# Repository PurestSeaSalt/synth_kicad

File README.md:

# synth_kicad
## GitHub Action to compile KiCad files

This repo contains an example custom PCB designed in KiCAD 5 with settings appropriate for PCB manufacture and assembly by JLCPCB. It also contains a GitHub workflow that generates the files needed by JLCPCB: gerbers, BOM, & position file. The workflow additionally generates a manual order BOM,  interactive BOM, and PDF export of the schematic. The manual order BOM includes components in the schematic not assembled by JLCPCB, such as board components not available through JLCPCB, enclosure, hardware, etc. The interactive BOM is an html document that assists in identifying component locations on the PCB for manual assembly.

## Setup Repository GitHub Actions Permissions

The workflow requires read/write access to the new repository to execute successfully.

In the new repository navigate to ```Settings```, and open the ```Actions``` > ```General``` page.

In the ```Workflow permissions``` section select ```Read and write permissions```

## New Repository Cleanup

The newly created repository will include the ```Example_Design``` example PCB design from the template repo. Files for this need to be removed and files for the new design need created. This is best done in a local clone of the new repository on your PC.

Using your Git client (Fork, GitHub Desktop, etc.) clone your new repository to a local folder on your PC.

Eventually this file, ```README.md```, should be replaced/updated with details for the new project. Consider keeping the ```Placing Orders``` and ```Failed Workflow Troubleshooting``` sections so instructions for ordering the design and troubleshooting workflow issues are readily available.

Update ```description``` and ```ownership``` entries in ```APM.yml```.

## New KiCAD Project Creation

Open the KiCAD 8 application.

In the KiCAD Project Manager select ```File``` > ```New``` > ```Project```.

In the ```Create New Project``` dialog check the box for ```Create a new directory for the project```. (Missing this step will break the GitHub workflow functionality.)

Navigate to the ```KiCadProjects``` folder under your cloned repository directory, Enter a name for your KiCAD project, and select ```Save```.

## KiCAD Schematic Setup

The GitHub workflow requires additional schematic symbol fields beyond the KiCAD defaults.

In the KiCAD schematic editor (Eeschema) select ```Preferences``` > ```Preferences...```

In the ```Eeschema``` > ```Field Name Templates``` section add the following entries:

- Part No
- Link
- LCSC
- Note

Check the ```URL``` box for the Link field.

This will add the above fields to every new symbol added to the schematic.

Note: These are KiCAD application settings and apply across all projects. If multiple users are contributing to the design, they will each need to apply these settings.

These fields can also be added to all current components in the KiCAD schematic editor under ```Tools``` > ```Edit Symbol Fields...```

For each component in the schematic either LCSC, for parts to be assembled by JLCPCB, or Part No, for parts to not be assembled by JLCPCB, must be filled out. Additionally the fields Link & Note can be filled out to provide additional information in the manually ordered parts BOM for parts to not be assembled by JLCPCB.

## KiCAD PCB Setup

The PCB design needs to be setup to match the capabilities of JLCPCB. These settings can be copied from the ```Example_Design``` in the template repo.

In the KiCAD PCB editor (PCBNew) select ```File``` > ```Board Setup...```

In the bottom left of the ```Board Setup dialog```, select ```Import Settings...```

In the bottom left of the ```Import Settings``` dialog click ```Select All```.

In the ```Import from``` field navigate to the folder ```KiCadProjects\Example_Design``` under your cloned repository directory and select ```Example_Design.pro```.

Select ```Import Settings```.

## Setup For Multiple Boards

Projects with more than one PCB, for example a motherboard and one or more daughter boards are supported. Follow the steps under ```New KiCAD Project Creation```, ```KiCAD Schematic Setup```, & ```KiCAD PCB Setup``` to create and setup a separate KiCad project for each board.

## Remove Example Design KiCad Project

After setting up the new KiCad project(s), the Example_Design files are no longer needed and the ```KiCadProjects\Example_Design``` folder can be deleted.

## Selecting Parts For JLCPCB Assembly

JLCPCB's parts catalog can be accessed at [jlcpcb.com/parts](https://jlcpcb.com/parts).

Prior to selecting parts for JLCPCB assembly it is recommended to review JLCPCB's PCB Assembly FAQs [Part 1](https://jlcpcb.com/help/article/98-pcb-assembly-faqs) & [Part 2](https://jlcpcb.com/help/article/39-pcb-assembly-faqs-part-2). Pay specific attention to the section related to Basic vs. Extended parts and the section related to polarity of components.

Recommended part selection priorities should be:

- Only SMD parts if possible (Avoid hand assembly & hand soldering fees)
- Prefer Basic parts vs. Extended parts (Avoid additional setup fees)
- Prefer parts with large inventories ( Avoid pre-order process. See ```NOTE``` under ```Placing Orders``` )

Once a part is selected enter the JLCPCB Part # in the LCSC field of the component in the KiCAD schematic.

## Notes on Footprint Rotation

JLCPCB uses the orientation of the component in the tape & reel when the feed direction is up as the zero degree reference. ( See JLCPCB's PCB Assembly FAQ [Part 2](https://jlcpcb.com/help/article/39-pcb-assembly-faqs-part-2). ) KiCAD uses the footprint orientation as the zero degree reference. For many standard component packages, common tape & reel orientations do not match the standard KiCAD footprint orientations. However, the position file generation tool of the GitHub workflow applies corrections for several standard packages to address this. ( See the internal list of rotations at the end of the [Notes about the position file](https://github.com/INTI-CMNB/KiBot#notes-about-the-position-file) section in the KiBot documentation. )

Consider an example design using an SOIC-8 component oriented with pin 1 at the top right. JLCPCB's PCB Assembly FAQ [Part 2](https://jlcpcb.com/help/article/39-pcb-assembly-faqs-part-2) indicates that for On Semiconductors SOIC-8 packages JLCPCB's zero orientation has pin 1 at the bottom-left, which would require a rotation of 180° to put pin 1 at the top-right.

KiCAD's default SOIC-8 footprint, ```SOIC-8_3.9x4.9mm_P1.27mm```, has pin 1 at the top-left. The footprint would be rotated 270° to put pin 1 at the top-right.

The footprint name, ```SOIC-8_3.9x4.9mm_P1.27mm```, matches the ```^SOIC-``` line in the internal list of rotations which adds 270° to the KiCAD rotation. This results in a total rotation of 180° in the position file, which matches the rotation expected by JLCPCB.

## Placing Orders

Prior to preparing to place orders, be sure all design changes are committed and pushed to the GitHub repository.

To generate files required for ordering parts navigate to the ```Issues``` page of the Github repository, and select ```New issue```.

To the right of ```Order and Assembly Files Request``` select ```Get started```.

Replace the ```[Your descriptor here]``` text in the title with a descriptor for your order. The beginning of the title must remain as ```Order and Assembly Files Request:``` in order to be processed.

Enter the quantity of boards you plan to order.

If applicable, select a board variant.

Select ```Submit new issue```.

A new run of the ```Process Order and Assembly Files Request``` workflow will be initiated. After a few minutes the run should complete. If successful the workflow run will add a comment with a link to the workflow run and close the issue. Open the workflow run to access the generated files. The workflow run can also be found under the repository's ```Actions``` page. The workflow run will have the same title as the requesting issue.

At the bottom of the workflow run page is a list of links to the generated files. Selecting ```Manual_Order_and_Assembly_Files``` will download a zip of the manual order BOM, interactive BOM, and schematic. Selecting ```JLCPCB_Files``` will download a zip file of the files needed for the JLCPCB order. These zip files will contain a subfolder for each KiCad project under ```KiCadProjects```.

```NOTE:``` If required parts are not in stock at JLCPCB you will need to use their pre-order process. Before ordering the PCB, parts not in JLCPCB's inventory must be ordered to your personal JLCPB parts library. When ordering these parts the initial price paid is an estimate. The parts will then be quoted. If the quote is less than the estimate the difference will be refunded. If the quote is greater than the estimate a supplemental payment must be made for the difference. The parts will then be purchased and delivered to your parts library at JLCPCB. Once all  parts are in JLCPCB's inventory or your parts library the PCB can be ordered. See [this](https://jlcpcb.com/help/article/49-how-to-build-your-own-parts-library-in-jlcpcb) JLCPCB help article for further details.

## Failed Workflow Troubleshooting

If the workflow run fails, showing a red X icon instead of a green check icon, first verify the request was filled out properly. Second look if the electrical rules check (ERC) and/or design rules check (DRC) failed. These workflow steps perform the same checks as the KiCAD schematic editor (Eescheema) for ERC and PCB editor (PCBNew) for DRC. Run these in the applications and clear all errors before proceeding.

The most common ERC error is a not driven pin error. Pins that have their ```Electrical type``` set as ```Power input``` such as power and ground pins, including the ```GND``` symbol must be connected to a pin with an ```Electrical type``` of ```Power output```. Often the symbol/pin where power & ground are supplied is a generic connector without a ```Power output``` pin. The ```PWR_FLAG``` symbol can be added to the schematic in these locations to clear this error.

## Board Variants

In certain cases it is desirable to have variability within a PCB design. Components may be added, excluded, or substituted as needed to meet various design needs. Variants can be supported through additional fields in the KiCAD schematic and minor modification of the GitHub workflow files.

NOTE: If variants are used by more than one KiCad project in the repo they must be common. When generating order files only one variant can be selected. Any project that does not have the selected variant defined will use the default variant.

### Defining Board Variants

Each board variant is identified by two unique names. One is the name used within KiCAD documents. The other is the name used by the GitHub workflow. These can (but, don't need to) be the same name. Two .yaml files in the repository need modification to define a new variant: ```Config.kibot.yaml``` and ```.github/ISSUE_TEMPLATE/Order_and_Assembly_Files_Request.yaml```.

In ```Config.kibot.yaml``` find the section below

```yaml
variants:
  - name: 'Default'
    comment: 'No variant applied'
    type: kibom
    pre_transform: '_rot_footprint'
```

The ```'Default'``` variant is already defined. This variant does not have any components added, excluded, or substituted. For each new variant add lines similar to below after the ```'Default'``` variant.

```yaml
  - name: 'Low_Spec_Variant'    # Workflow name of variant.
    comment: 'Feature reduced version of design'    # Short description of variant.
    type: kibom    # Do not change this.
    file_id: _Low_Spec    #Suffix included in filename for files generated with this variant.
    variant: Low_Spec    #KiCAD name of variant.
    pre_transform:    # Do not change these.
      - '_var_rename'
      - '_rot_footprint'
```

Insure ```- name``` of the new variant is indented the same as ```- name``` of the default variant and all indentation relative to ```- name``` is maintained as shown here.

Set ```name```, ```comment```, ```file_id```, and ```variant``` to appropriate values. Only ```comment``` may include spaces.

In ```.github/ISSUE_TEMPLATE/Order_and_Assembly_Files_Request.yaml``` find the section below

```yaml
  - type: dropdown
    id: Board_Variant
    attributes:
      label: 'Board_Variant'
      multiple: false
      options:
        - 'Default'
```

For each new variant add a line consisting of '```- [Workflow Name of Variant]```' below and at the same indentation lavel as ```-'Default'``` where ```[Workflow Name of Variant]``` matches the value of ```name``` that was entered in ```Config.kibot.yaml```.

For example, ```- 'Low_Spec_Variant'```

### Adding / Excluding Components In Variants

For any component that is added or excluded from any specific variants, add a field named Config to the symbol in the KiCAD schematic. To add a component to a specific variant enter ```+[KiCAD Name of Variant]``` in the Config field. To remove a component from a specific variant enter ```-[KiCAD Name of Variant]``` in the Config field. If a component is added or removed from multiple variants they can each be added separated by a comma.

For example if R1 should be present in the ```Default``` variant, but not in ```VariantOne``` or ```VariantTwo``` and R2 should be present only in ```VariantTwo``` then the Config field for the two components should be:

|Reference|Config|
|---|---|
|R1|-VariantOne, -VariantTwo|
|R2|+VariantTwo|

### Replacing Components In Variants

To replace a component the default and substituted part(s) must share a common schematic symbol and footprint. The substituted part will have different values for fields like: Value, Part No, LCSC and possibly others. This is accomplished by adding a new field which is named as ```[KiCAD Name of Variant]```:```[Name of Field To Replace]```. A component may have the same or different substituted parts for each variant.

For example if D1 is a green LED with a JLCPCB part # of C2297 and is to be replaced with a red LED with a JLCPCB Part # of C84256 in variant Red_LED, or a yellow LED with a JLCPCB Part # of C2296 in variant Yellow_LED, then the LCSC field would have a value of C2297. Additional fields RED_LED:LCSC with a value of C84256 and Yellow_LED:LCSC with a value of C2296 would be added.

|Reference|LCSC|Red_LED:LCSC|Yellow_LED:LCSC|
|---|---|---|---|
|D1|C2297|C84256|C2296|

## Credits

The GitHub workflow in this repository relies on the KiBot project. [INTI-CMNB/KiBot](https://github.com/INTI-CMNB/KiBot)

## Useful References

KiCAD Tutorial: [Intro to KiCAD - YouTube](https://www.youtube.com/playlist?list=PLEBQazB0HUyR24ckSZ5u05TZHV9khgA1O)

JLCPCB Parts Catalog: [jlcpcb.com/parts](https://jlcpcb.com/parts)

JLCPCB Help Articles: [jlcpcb.com/help/catalog](https://jlcpcb.com/help/catalog)

KiBot GitHub Page [INTI-CMNB/KiBot](https://github.com/INTI-CMNB/KiBot)

easyeda2kicad GitHub Page [easyeda2kicad.py](https://github.com/uPesy/easyeda2kicad.py)

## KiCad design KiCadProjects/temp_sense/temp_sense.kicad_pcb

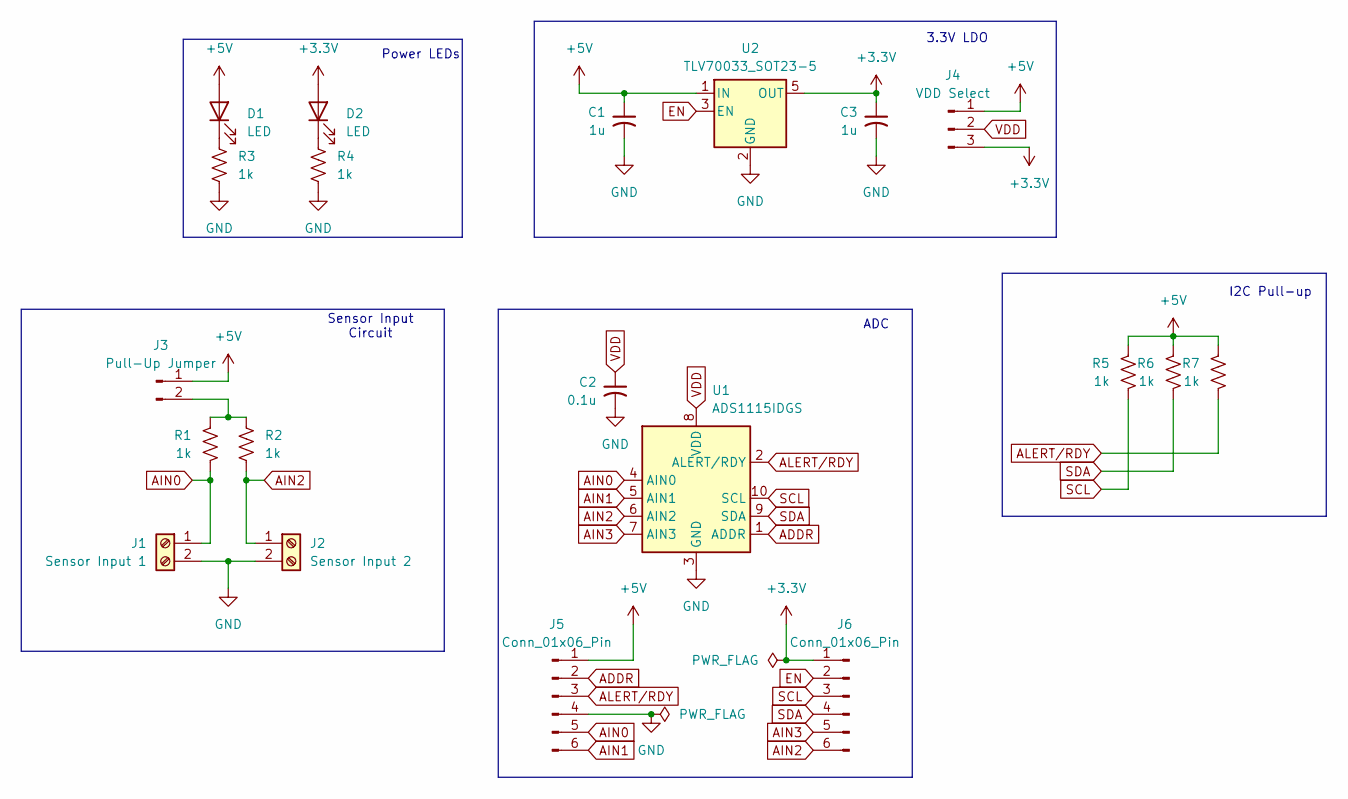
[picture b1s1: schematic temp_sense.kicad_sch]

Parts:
C1, C3: 1u; C_0603_1608Metric_Pad1.08x0.95mm_HandSolder; LCSC C15849
C2: 0.1u; C_0603_1608Metric_Pad1.08x0.95mm_HandSolder; LCSC C14663
D1, D2: LED; LED_0603_1608Metric; LCSC C19171390
J1: Sensor Input 1; TerminalBlock_TE_282834-2_1x02_P2.54mm_Horizontal
J2: Sensor Input 2; TerminalBlock_TE_282834-2_1x02_P2.54mm_Horizontal
J3: Pull-Up Jumper; PinHeader_1x02_P2.54mm_Vertical
J4: VDD Select; PinHeader_1x03_P2.54mm_Vertical
J5, J6: Conn_01x06_Pin; PinHeader_1x06_P2.54mm_Vertical
R1, R2, R3, R4, R5, R6, R7: 1k; R_0603_1608Metric_Pad0.98x0.95mm_HandSolder; LCSC C22548
U1: ADS1115IDGS; TSSOP-10_3x3mm_P0.5mm; LCSC C37593
U2: TLV70033_SOT23-5; SOT-23-5; LCSC C11337

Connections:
+3.3V: C3.1, D2.2 (A), J4.3, J6.1, U2.5 (OUT)
+5V: C1.1, D1.2 (A), J3.1, J4.1, J5.1, R5.1, R6.1, R7.1, U2.1 (IN)
ADDR: J5.2, U1.1 (ADDR)
AIN0: J1.1, J5.5, R1.2, U1.4 (AIN0)
AIN1: J5.6, U1.5 (AIN1)
AIN2: J2.1, J6.6, R2.2, U1.6 (AIN2)
AIN3: J6.5, U1.7 (AIN3)
ALERT/RDY: J5.3, R7.2, U1.2 (ALERT/RDY)
EN: J6.2, U2.3 (EN)
GND: C1.2, C2.2, C3.2, J1.2, J2.2, J5.4, R3.2, R4.2, U1.3 (GND), U2.2 (GND)
unnamed: D1.1 (K), R3.1
unnamed: D2.1 (K), R4.1
unnamed: J3.2, R1.1, R2.1
SCL: J6.3, R5.2, U1.10 (SCL)
SDA: J6.4, R6.2, U1.9 (SDA)
VDD: C2.1, J4.2, U1.8 (VDD)

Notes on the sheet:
I2C Pull-up
Sensor Input Circuit
Power LEDs
3.3V LDO
ADC

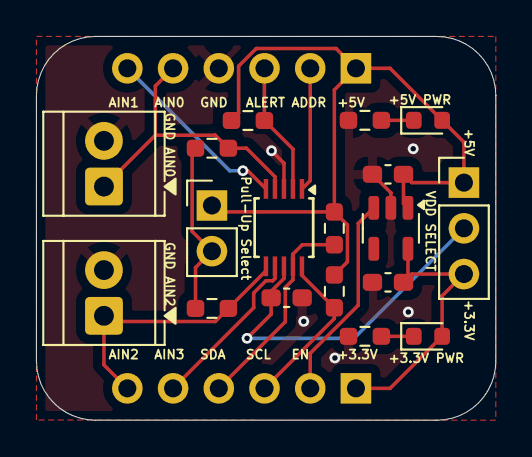
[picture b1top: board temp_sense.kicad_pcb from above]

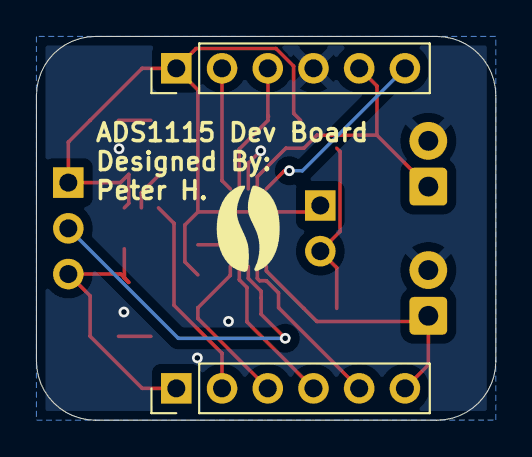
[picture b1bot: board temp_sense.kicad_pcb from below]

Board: 2 copper layers, 25.5 x 21.3 mm, 20 parts (2 on the bottom side), 16 nets.

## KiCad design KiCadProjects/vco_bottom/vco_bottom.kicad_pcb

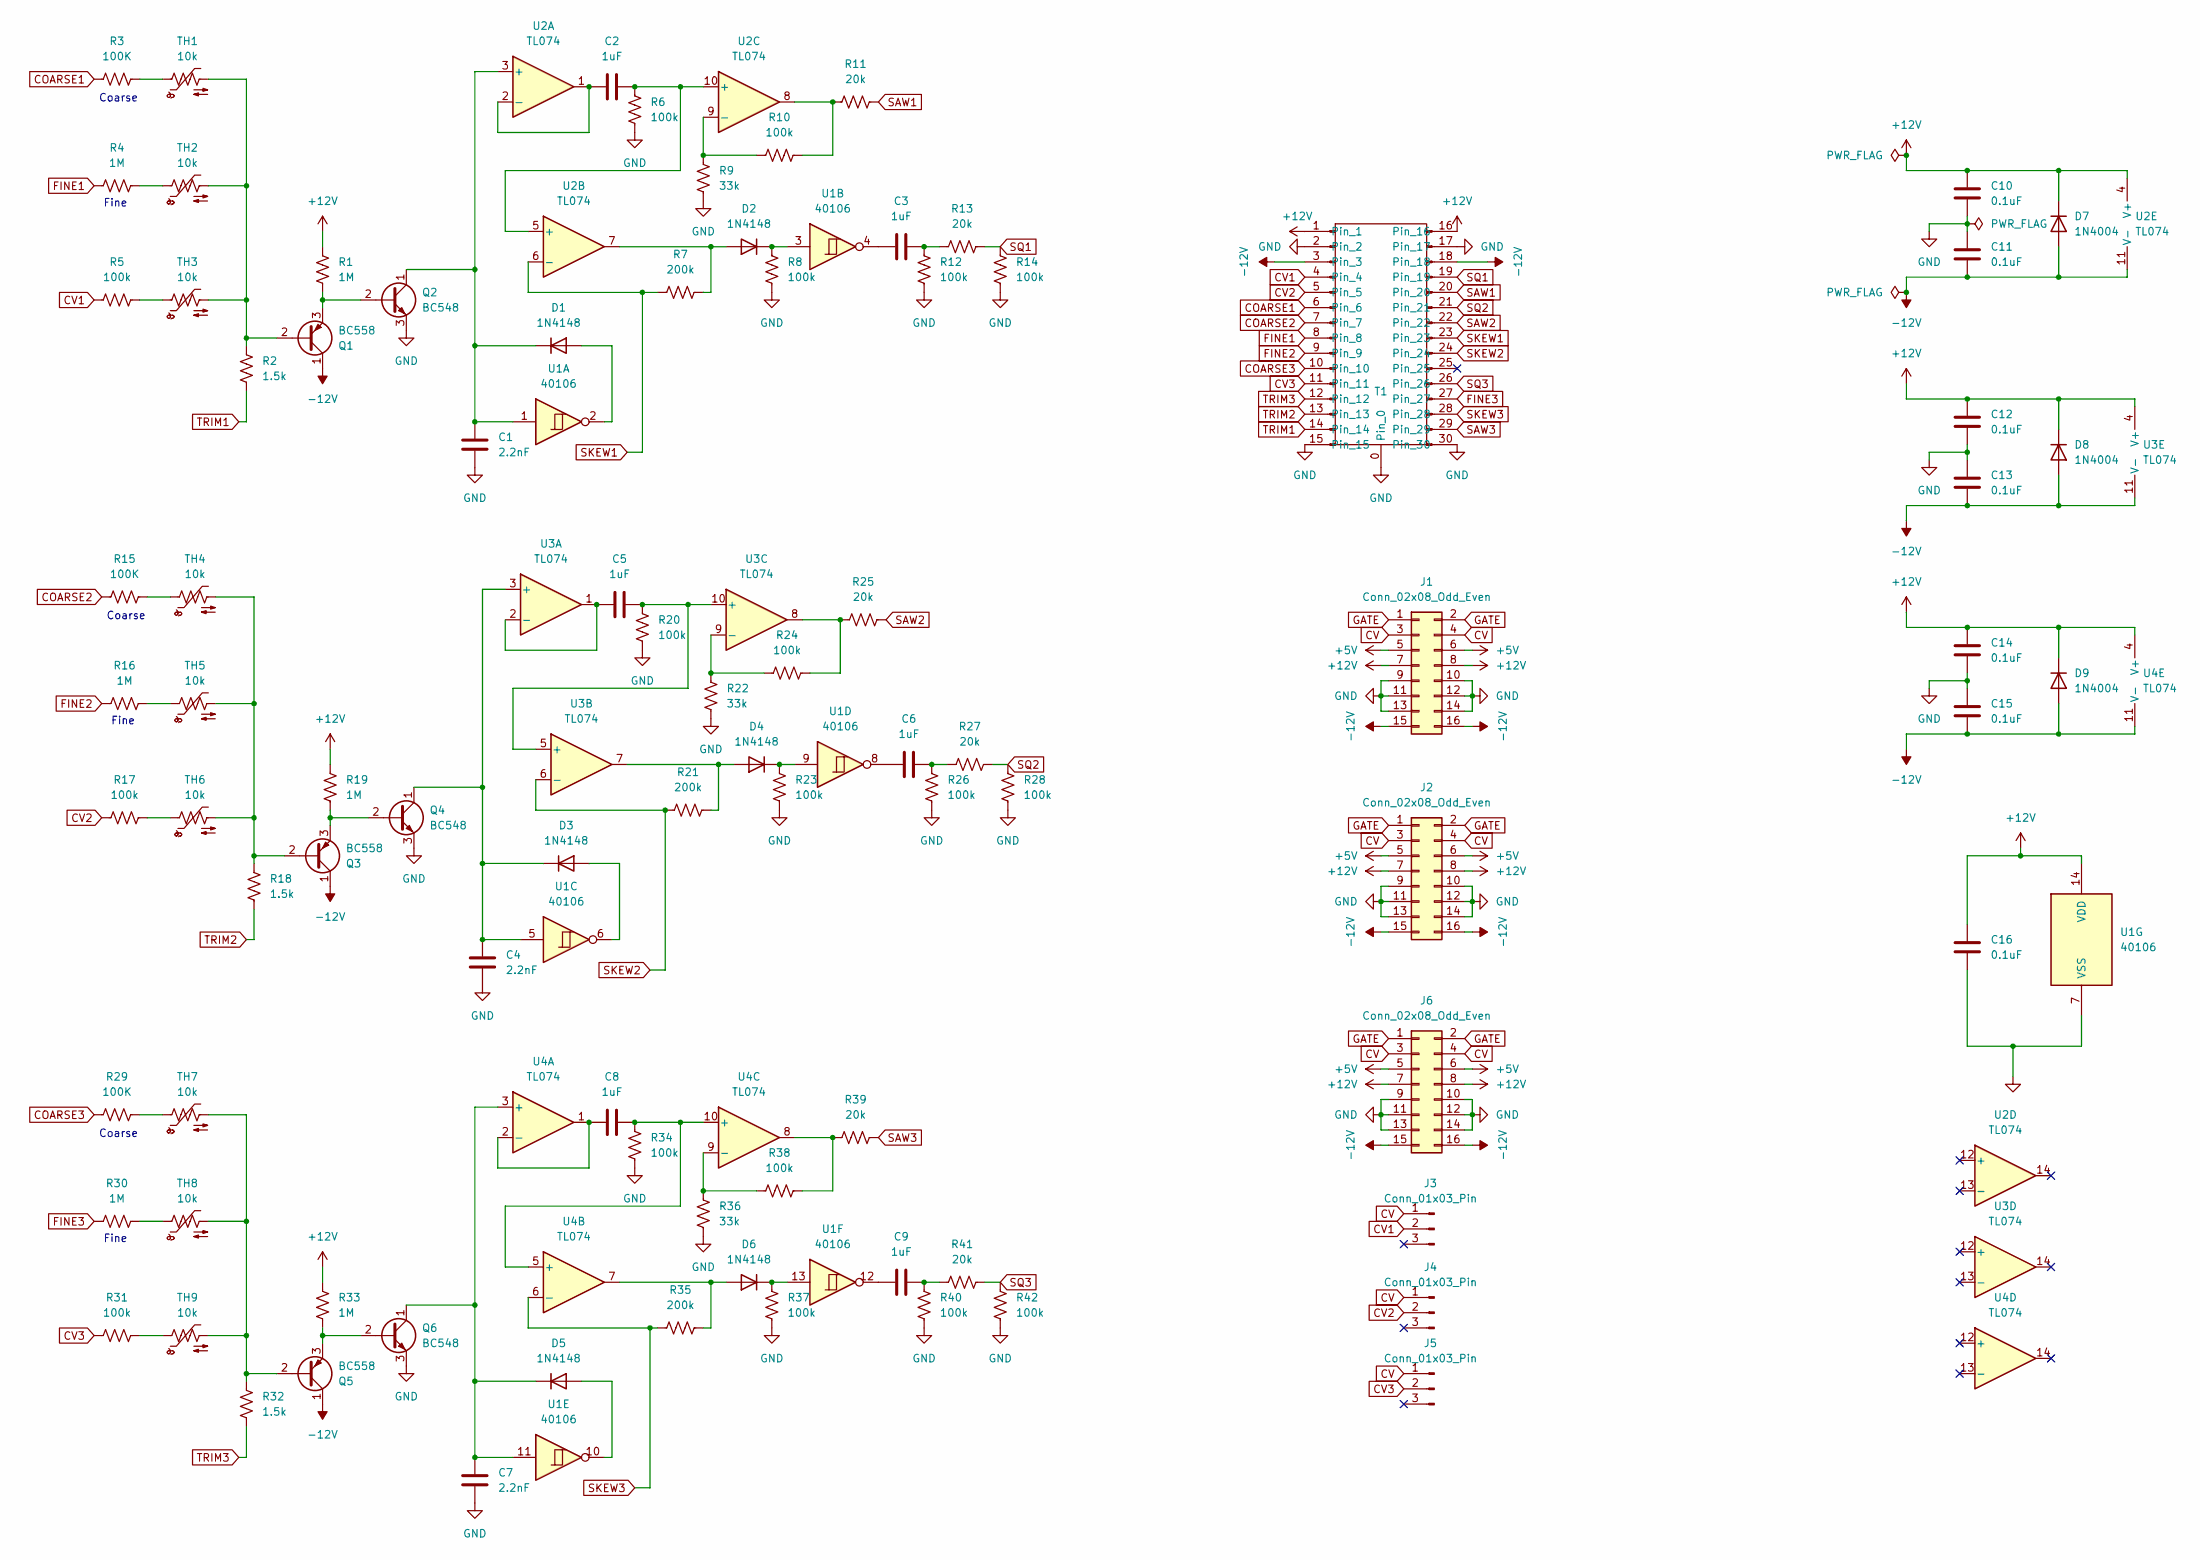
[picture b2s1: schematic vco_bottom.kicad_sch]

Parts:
C1, C4, C7: 2.2nF; C_Disc_D5.0mm_W2.5mm_P5.00mm
C2, C3, C5, C6, C8, C9: 1uF; C_Disc_D5.0mm_W2.5mm_P5.00mm
C10, C11, C12, C13, C14, C15, C16: 0.1uF; C_Disc_D5.0mm_W2.5mm_P5.00mm; Part No. 399-4148-ND
D1, D2, D3, D4, D5, D6: 1N4148; D_DO-35_SOD27_P7.62mm_Horizontal
D7, D8, D9: 1N4004; D_DO-41_SOD81_P10.16mm_Horizontal; Part No. 4878-1N4004CT-ND
J1, J2, J6: Conn_02x08_Odd_Even; PinHeader_2x08_P2.54mm_Vertical; Part No. A26270-ND
J3, J4, J5: Conn_01x03_Pin; PinHeader_1x03_P2.54mm_Vertical
Q1, Q3, Q5: BC558; TO-92_Inline
Q2, Q4, Q6: BC548; TO-92_Inline
R1, R4, R16, R19, R30, R33: 1M; R_Axial_DIN0207_L6.3mm_D2.5mm_P7.62mm_Horizontal
R2, R18, R32: 1.5k; R_Axial_DIN0207_L6.3mm_D2.5mm_P7.62mm_Horizontal
R3, R15, R29: 100K; R_Axial_DIN0207_L6.3mm_D2.5mm_P7.62mm_Horizontal
R5, R6, R8, R10, R12, R14, R17, R20, R23, R24, R26, R28, R31, R34, R37, R38, R40, R42: 100k; R_Axial_DIN0207_L6.3mm_D2.5mm_P7.62mm_Horizontal
R7, R21, R35: 200k; R_Axial_DIN0207_L6.3mm_D2.5mm_P7.62mm_Horizontal
R9, R22, R36: 33k; R_Axial_DIN0207_L6.3mm_D2.5mm_P7.62mm_Horizontal
R11, R13, R25, R27, R39, R41: 20k; R_Axial_DIN0207_L6.3mm_D2.5mm_P7.62mm_Horizontal
T1: template_32U
TH1, TH2, TH3, TH4, TH5, TH6, TH7, TH8, TH9: 10k; R_Axial_DIN0207_L6.3mm_D2.5mm_P7.62mm_Horizontal
U1: 40106; DIP-14_W7.62mm_Socket
U2, U3, U4: TL074; DIP-14_W7.62mm_Socket

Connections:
+5V: J1.5, J1.6, J2.5, J2.6, J6.5, J6.6
+12V: C10.1, C12.1, C14.1, C16.1, D7.1 (K), D8.1 (K), D9.1 (K), J1.7, J1.8, J2.7, J2.8, J6.7, J6.8, R1.1, R19.1, R33.1, T1.1, T1.16, U1.14 (VDD), U2.4 (V+), U3.4 (V+), U4.4 (V+)
-12V: C11.2, C13.2, C15.2, D7.2 (A), D8.2 (A), D9.2 (A), J1.15, J1.16, J2.15, J2.16, J6.15, J6.16, Q1.1 (C), Q3.1 (C), Q5.1 (C), T1.3, T1.18, U2.11 (V-), U3.11 (V-), U4.11 (V-)
COARSE1: R3.2, T1.6
COARSE2: R15.2, T1.7
COARSE3: R29.2, T1.10
CV: J1.3, J1.4, J2.3, J2.4, J3.1, J4.1, J5.1, J6.3, J6.4
CV1: J3.2, R5.1, T1.4
CV2: J4.2, R17.1, T1.5
CV3: J5.2, R31.1, T1.11
FINE1: R4.1, T1.8
FINE2: R16.1, T1.9
FINE3: R30.1, T1.27
GATE: J1.1, J1.2, J2.1, J2.2, J6.1, J6.2
GND: C1.2, C4.2, C7.2, C10.2, C11.1, C12.2, C13.1, C14.2, C15.1, C16.2, J1.9, J1.10, J1.11, J1.12, J1.13, J1.14, J2.9, J2.10, J2.11, J2.12, J2.13, J2.14, J6.9, J6.10, J6.11, J6.12, J6.13, J6.14, Q2.3 (E), Q4.3 (E), Q6.3 (E), R6.2, R8.2, R9.2, R12.2, R14.2, R20.2, R22.2, R23.2, R26.2, R28.2, R34.2, R36.2, R37.2, R40.2, R42.2, T1.0, T1.2, T1.15, T1.17, T1.30, U1.7 (VSS)
unnamed: C3.1, U1.4
unnamed: C3.2, R12.1, R13.1
unnamed: C6.1, U1.8
unnamed: C6.2, R26.1, R27.1
unnamed: C9.1, U1.12
unnamed: C9.2, R40.1, R41.1
unnamed: D1.2 (A), U1.2
unnamed: C1.1, D1.1 (K), Q2.1 (C), U1.1, U2.3 (+)
unnamed: D2.2 (A), R7.1, U2.7
unnamed: D2.1 (K), R8.1, U1.3
unnamed: D3.2 (A), U1.6
unnamed: C4.1, D3.1 (K), Q4.1 (C), U1.5, U3.3 (+)
unnamed: D4.2 (A), R21.1, U3.7
unnamed: D4.1 (K), R23.1, U1.9
unnamed: D5.2 (A), U1.10
unnamed: C7.1, D5.1 (K), Q6.1 (C), U1.11, U4.3 (+)
unnamed: D6.2 (A), R35.1, U4.7
unnamed: D6.1 (K), R37.1, U1.13
unnamed: Q1.2 (B), R2.1, TH1.2, TH2.2, TH3.2
unnamed: Q1.3 (E), Q2.2 (B), R1.2
unnamed: Q3.2 (B), R18.1, TH4.2, TH5.2, TH6.2
unnamed: Q3.3 (E), Q4.2 (B), R19.2
unnamed: Q5.2 (B), R32.1, TH7.2, TH8.2, TH9.2
unnamed: Q5.3 (E), Q6.2 (B), R33.2
unnamed: R3.1, TH1.1
unnamed: R4.2, TH2.1
unnamed: R5.2, TH3.1
unnamed: R10.2, R11.1, U2.8
unnamed: R15.1, TH4.1
unnamed: R16.2, TH5.1
unnamed: R17.2, TH6.1
unnamed: R24.2, R25.1, U3.8
unnamed: R29.1, TH7.1
unnamed: R30.2, TH8.1
unnamed: R31.2, TH9.1
unnamed: R38.2, R39.1, U4.8
unnamed: C2.1, U2.1, U2.2 (-)
unnamed: C2.2, R6.1, U2.5 (+), U2.10 (+)
unnamed: R9.1, R10.1, U2.9 (-)
unnamed: C5.1, U3.1, U3.2 (-)
unnamed: C5.2, R20.1, U3.5 (+), U3.10 (+)
unnamed: R22.1, R24.1, U3.9 (-)
unnamed: C8.1, U4.1, U4.2 (-)
unnamed: C8.2, R34.1, U4.5 (+), U4.10 (+)
unnamed: R36.1, R38.1, U4.9 (-)
SAW1: R11.2, T1.20
SAW2: R25.2, T1.22
SAW3: R39.2, T1.29
SKEW1: R7.2, T1.23, U2.6 (-)
SKEW2: R21.2, T1.24, U3.6 (-)
SKEW3: R35.2, T1.28, U4.6 (-)
SQ1: R13.2, R14.1, T1.19
SQ2: R27.2, R28.1, T1.21
SQ3: R41.2, R42.1, T1.26
TRIM1: R2.2, T1.14
TRIM2: R18.2, T1.13
TRIM3: R32.2, T1.12

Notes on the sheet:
Fine
Coarse

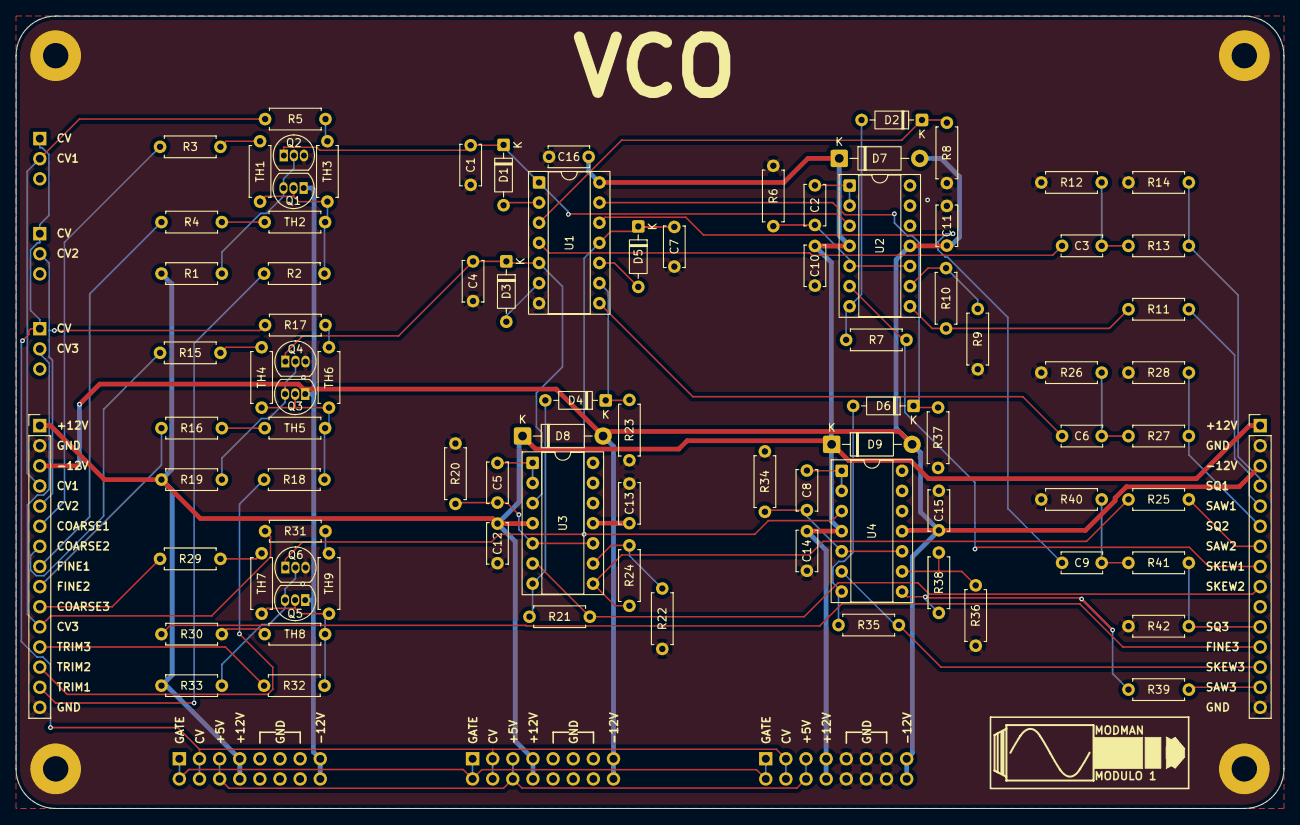
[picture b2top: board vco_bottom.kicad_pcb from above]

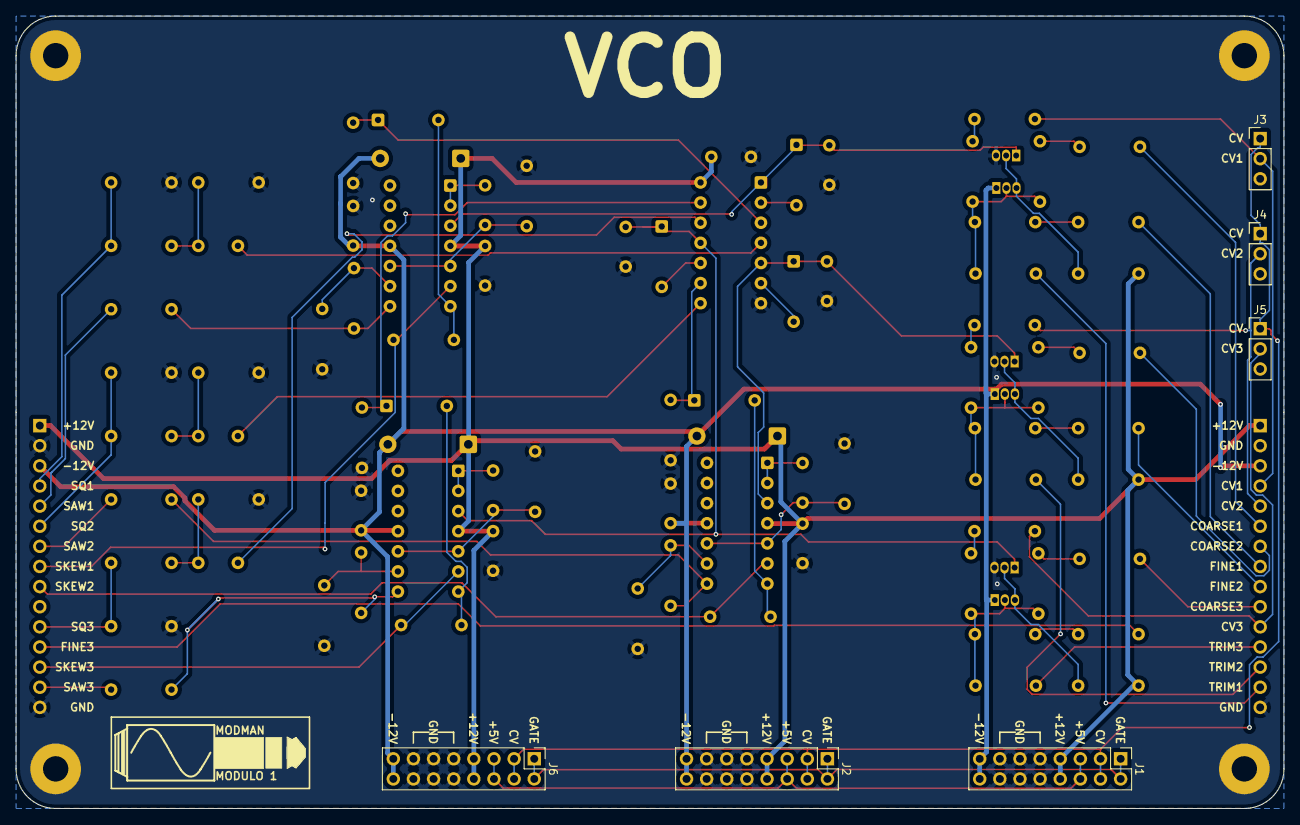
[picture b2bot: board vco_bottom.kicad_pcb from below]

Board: 2 copper layers, 160.0 x 100.0 mm, 93 parts (6 on the bottom side), 72 nets.

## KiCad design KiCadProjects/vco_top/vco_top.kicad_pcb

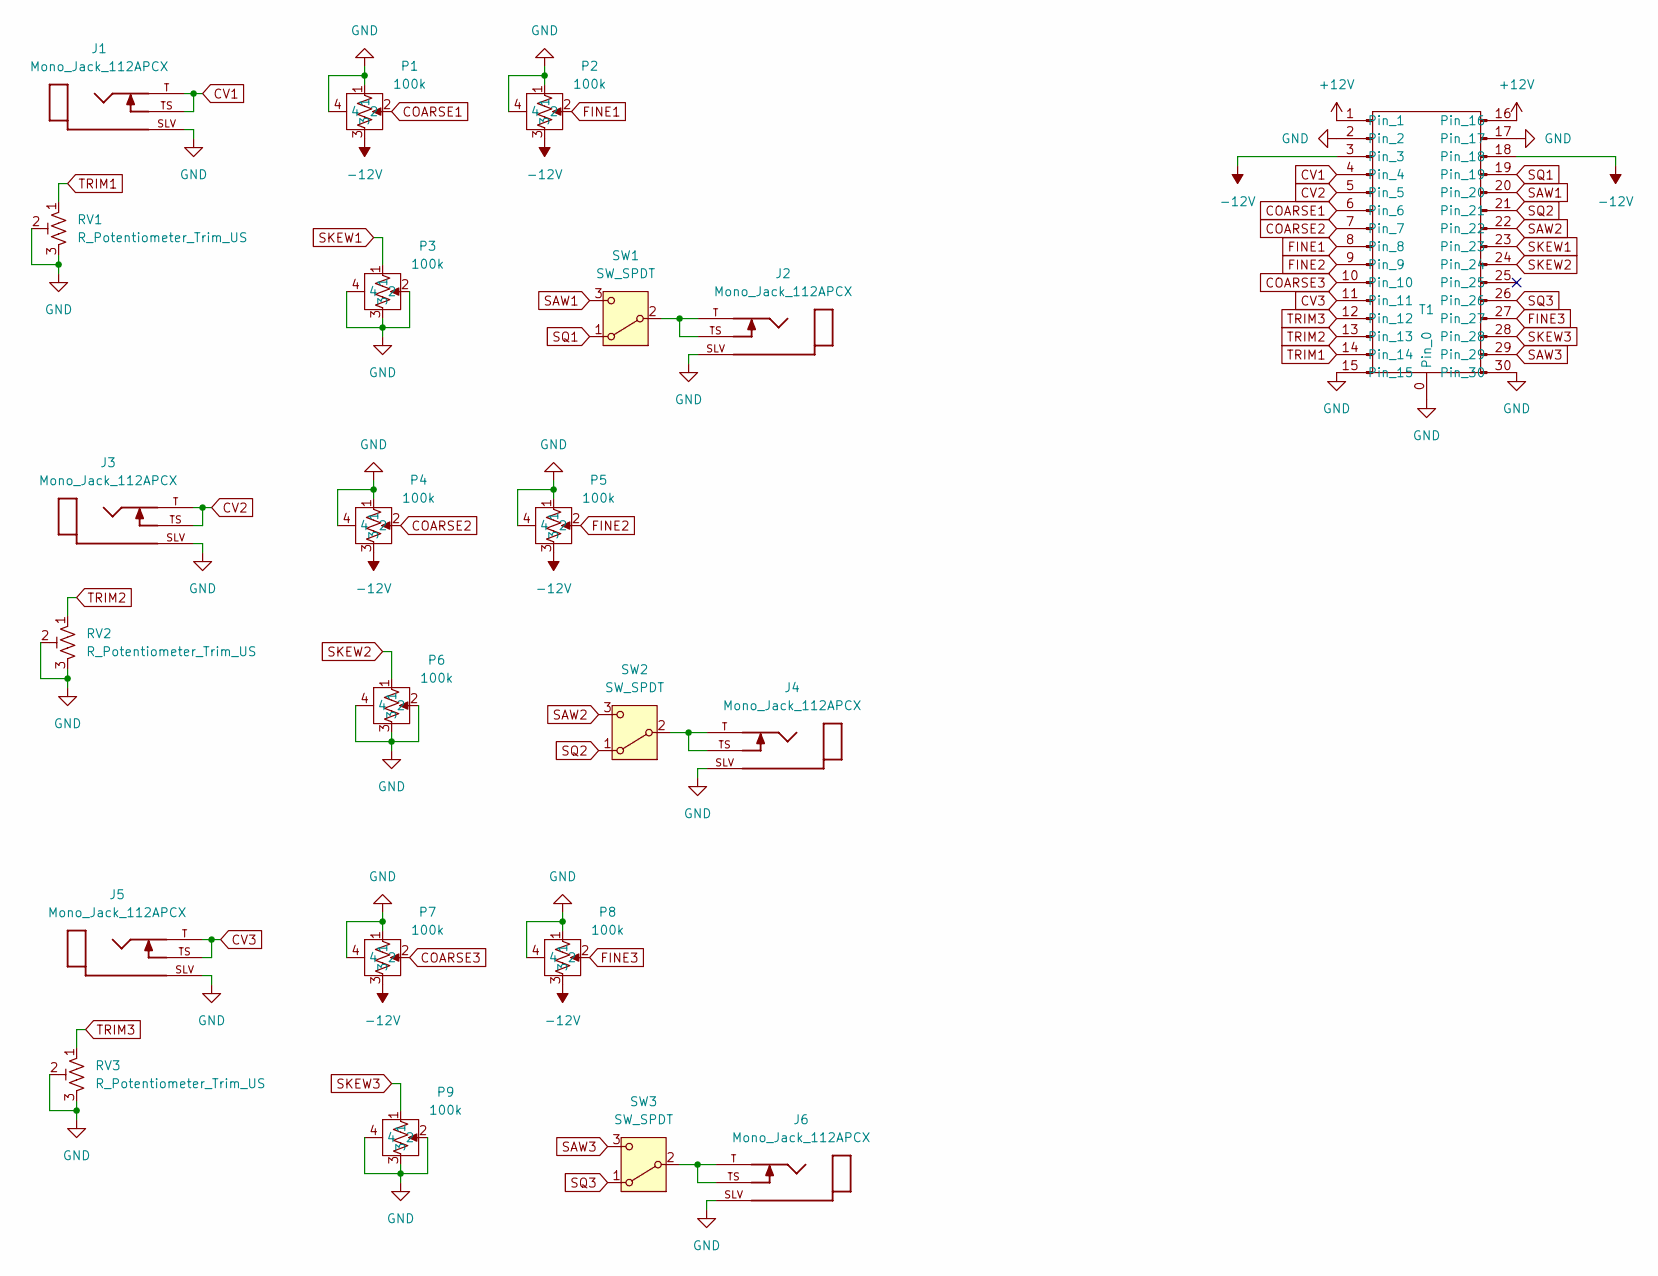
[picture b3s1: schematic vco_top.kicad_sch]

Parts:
J1, J2, J3, J4, J5, J6: Mono_Jack_112APCX; PARTREV A
P1, P2, P3, P4, P5, P6, P7, P8, P9: 100k; Potentiometer_SG_Bourns; Part No. PDB12-M4251-104BF-ND
RV1, RV2, RV3: R_Potentiometer_Trim_US; Potentiometer_Bourns_3266P_Horizontal
SW1, SW2, SW3: SW_SPDT; SW_100SP1T1B4M2QE; Part No. EG2355-ND
T1: template_32U

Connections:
+12V: T1.1, T1.16
-12V: P1.3, P2.3, P4.3, P5.3, P7.3, P8.3, T1.3, T1.18
COARSE1: P1.2, T1.6
COARSE2: P4.2, T1.7
COARSE3: P7.2, T1.10
CV1: J1.T, J1.TS, T1.4
CV2: J3.T, J3.TS, T1.5
CV3: J5.T, J5.TS, T1.11
FINE1: P2.2, T1.8
FINE2: P5.2, T1.9
FINE3: P8.2, T1.27
GND: J1.SLV, J2.SLV, J3.SLV, J4.SLV, J5.SLV, J6.SLV, P1.1, P1.4, P2.1, P2.4, P3.2, P3.3, P3.4, P4.1, P4.4, P5.1, P5.4, P6.2, P6.3, P6.4, P7.1, P7.4, P8.1, P8.4, P9.2, P9.3, P9.4, RV1.2, RV1.3, RV2.2, RV2.3, RV3.2, RV3.3, T1.0, T1.2, T1.15, T1.17, T1.30
unnamed: J2.T, J2.TS, SW1.2 (B)
unnamed: J4.T, J4.TS, SW2.2 (B)
unnamed: J6.T, J6.TS, SW3.2 (B)
SAW1: SW1.3 (C), T1.20
SAW2: SW2.3 (C), T1.22
SAW3: SW3.3 (C), T1.29
SKEW1: P3.1, T1.23
SKEW2: P6.1, T1.24
SKEW3: P9.1, T1.28
SQ1: SW1.1 (A), T1.19
SQ2: SW2.1 (A), T1.21
SQ3: SW3.1 (A), T1.26
TRIM1: RV1.1, T1.14
TRIM2: RV2.1, T1.13
TRIM3: RV3.1, T1.12

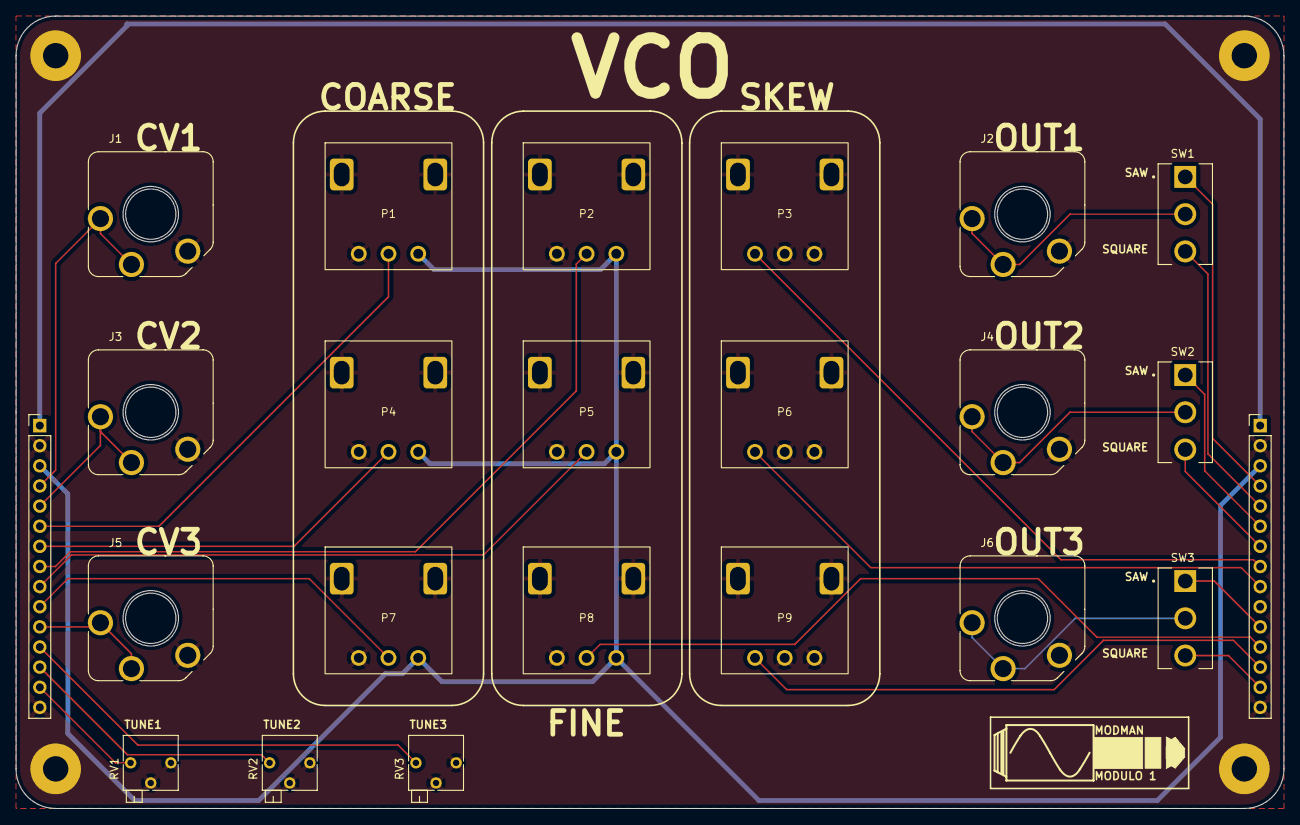
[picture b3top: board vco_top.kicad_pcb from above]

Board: 2 copper layers, 160.0 x 100.0 mm, 22 parts (0 on the bottom side), 27 nets.

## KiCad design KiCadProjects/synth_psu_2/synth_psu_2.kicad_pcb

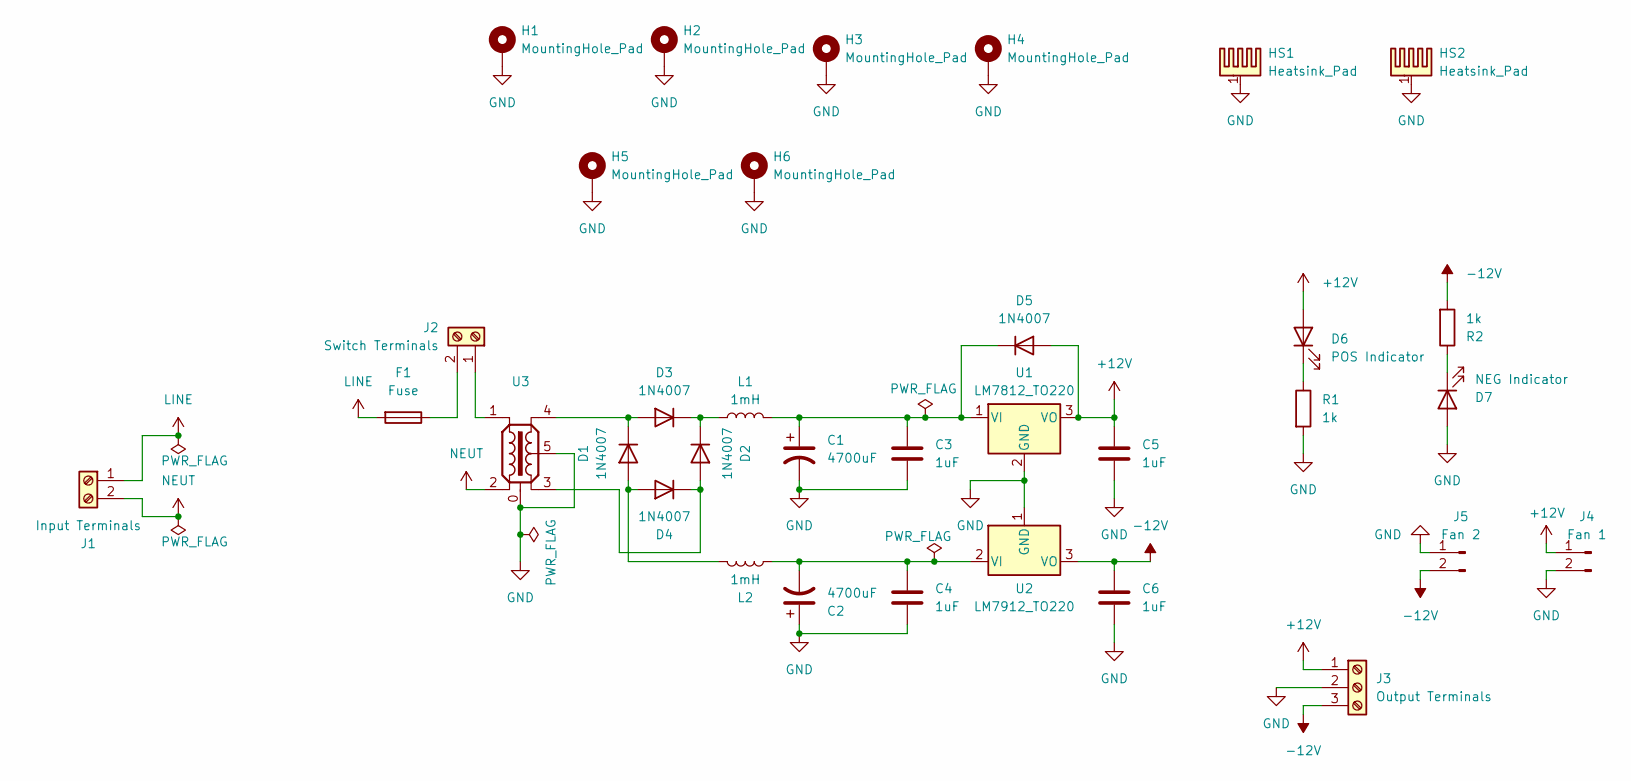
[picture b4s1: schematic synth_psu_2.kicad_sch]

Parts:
C1, C2: 4700uF; CP_Radial_D18.0mm_P7.50mm; Part No. 1189-1397-ND
C3, C4, C5, C6: 1uF; C_Disc_D5.0mm_W2.5mm_P5.00mm; Part No. 399-9886-1-ND
D1, D2, D3, D4, D5: 1N4007; D_DO-41_SOD81_P10.16mm_Horizontal; Part No. 4878-1N4007CT-ND
D6: POS Indicator; LED_D5.0mm; Part No. 732-5016-ND
D7: NEG Indicator; LED_D5.0mm; Part No. 732-5016-ND
F1: Fuse; Fuseholder_Clip-5x20mm_Littelfuse_100_Inline_P20.50x4.60mm_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; Part No. F6094-ND
H1, H2, H3, H4, H5, H6: MountingHole_Pad; MountingHole_4.3mm_M4_Pad
HS1, HS2: Heatsink_Pad; heatsink; Part No. RA-T2X-38E-ND
J1: Input Terminals; TerminalBlock_TE_282834-2_1x02_P2.54mm_Horizontal; Part No. A98333-ND
J2: Switch Terminals; TerminalBlock_TE_282834-2_1x02_P2.54mm_Horizontal; Part No. A98333-ND
J3: Output Terminals; TerminalBlock_TE_282834-3_1x03_P2.54mm_Horizontal; Part No. A98334-ND
J4: Fan 1; PinHeader_1x02_P2.54mm_Vertical; Part No. 952-2262-ND
J5: Fan 2; PinHeader_1x02_P2.54mm_Vertical; Part No. 952-2262-ND
L1, L2: 1mH; L_Toroid_Vertical_L21.6mm_W11.4mm_P7.62mm_Pulse_KM-3; Part No. M8863-ND
R1, R2: 1k; R_Axial_DIN0207_L6.3mm_D2.5mm_P7.62mm_Horizontal; Part No. CF12JT1K00CT-ND
U1: LM7812_TO220; TO-220-3_Vertical; Part No. 296-50628-ND
U2: LM7912_TO220; TO-220-3_Vertical; Part No. LM7912CT/NOPB-ND
U3: transformer; Part No. 595-1056-ND

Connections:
+12V: C5.1, D5.2 (A), D6.2 (A), J3.1, J4.1, U1.3 (VO)
-12V: C6.1, J3.3, J5.2, R2.2, U2.3 (VO)
GND: C1.2, C2.1, C3.2, C4.2, C5.2, C6.2, D7.2 (A), H1.1, H2.1, H3.1, H4.1, H5.1, H6.1, HS1.1, HS2.1, J3.2, J4.2, J5.1, R1.2, U1.2 (GND), U2.1 (GND), U3.0, U3.5
LINE: F1.2, J1.1
NEUT: J1.2, U3.2
unnamed: D1.2 (A), D4.2 (A), L2.1
unnamed: D1.1 (K), D3.2 (A), U3.4
unnamed: D2.2 (A), D4.1 (K), U3.3
unnamed: D2.1 (K), D3.1 (K), L1.1
unnamed: C1.1, C3.1, D5.1 (K), L1.2, U1.1 (VI)
unnamed: D6.1 (K), R1.1
unnamed: D7.1 (K), R2.1
unnamed: J2.1, U3.1
unnamed: F1.1, J2.2
unnamed: C2.2, C4.1, L2.2, U2.2 (VI)

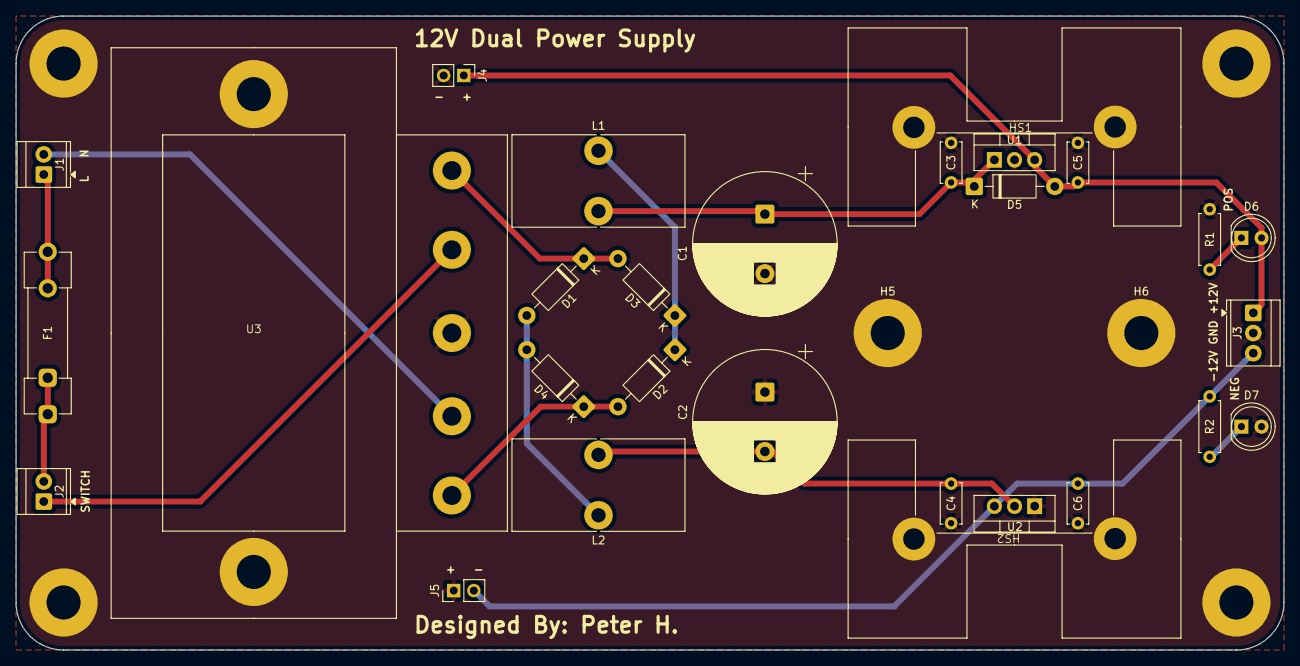
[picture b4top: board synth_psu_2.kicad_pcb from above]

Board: 2 copper layers, 160.0 x 80.0 mm, 34 parts (0 on the bottom side), 15 nets.
